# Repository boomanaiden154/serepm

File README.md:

# SeRepM

Like RepRap, but intended to (maybe) actually build itself.

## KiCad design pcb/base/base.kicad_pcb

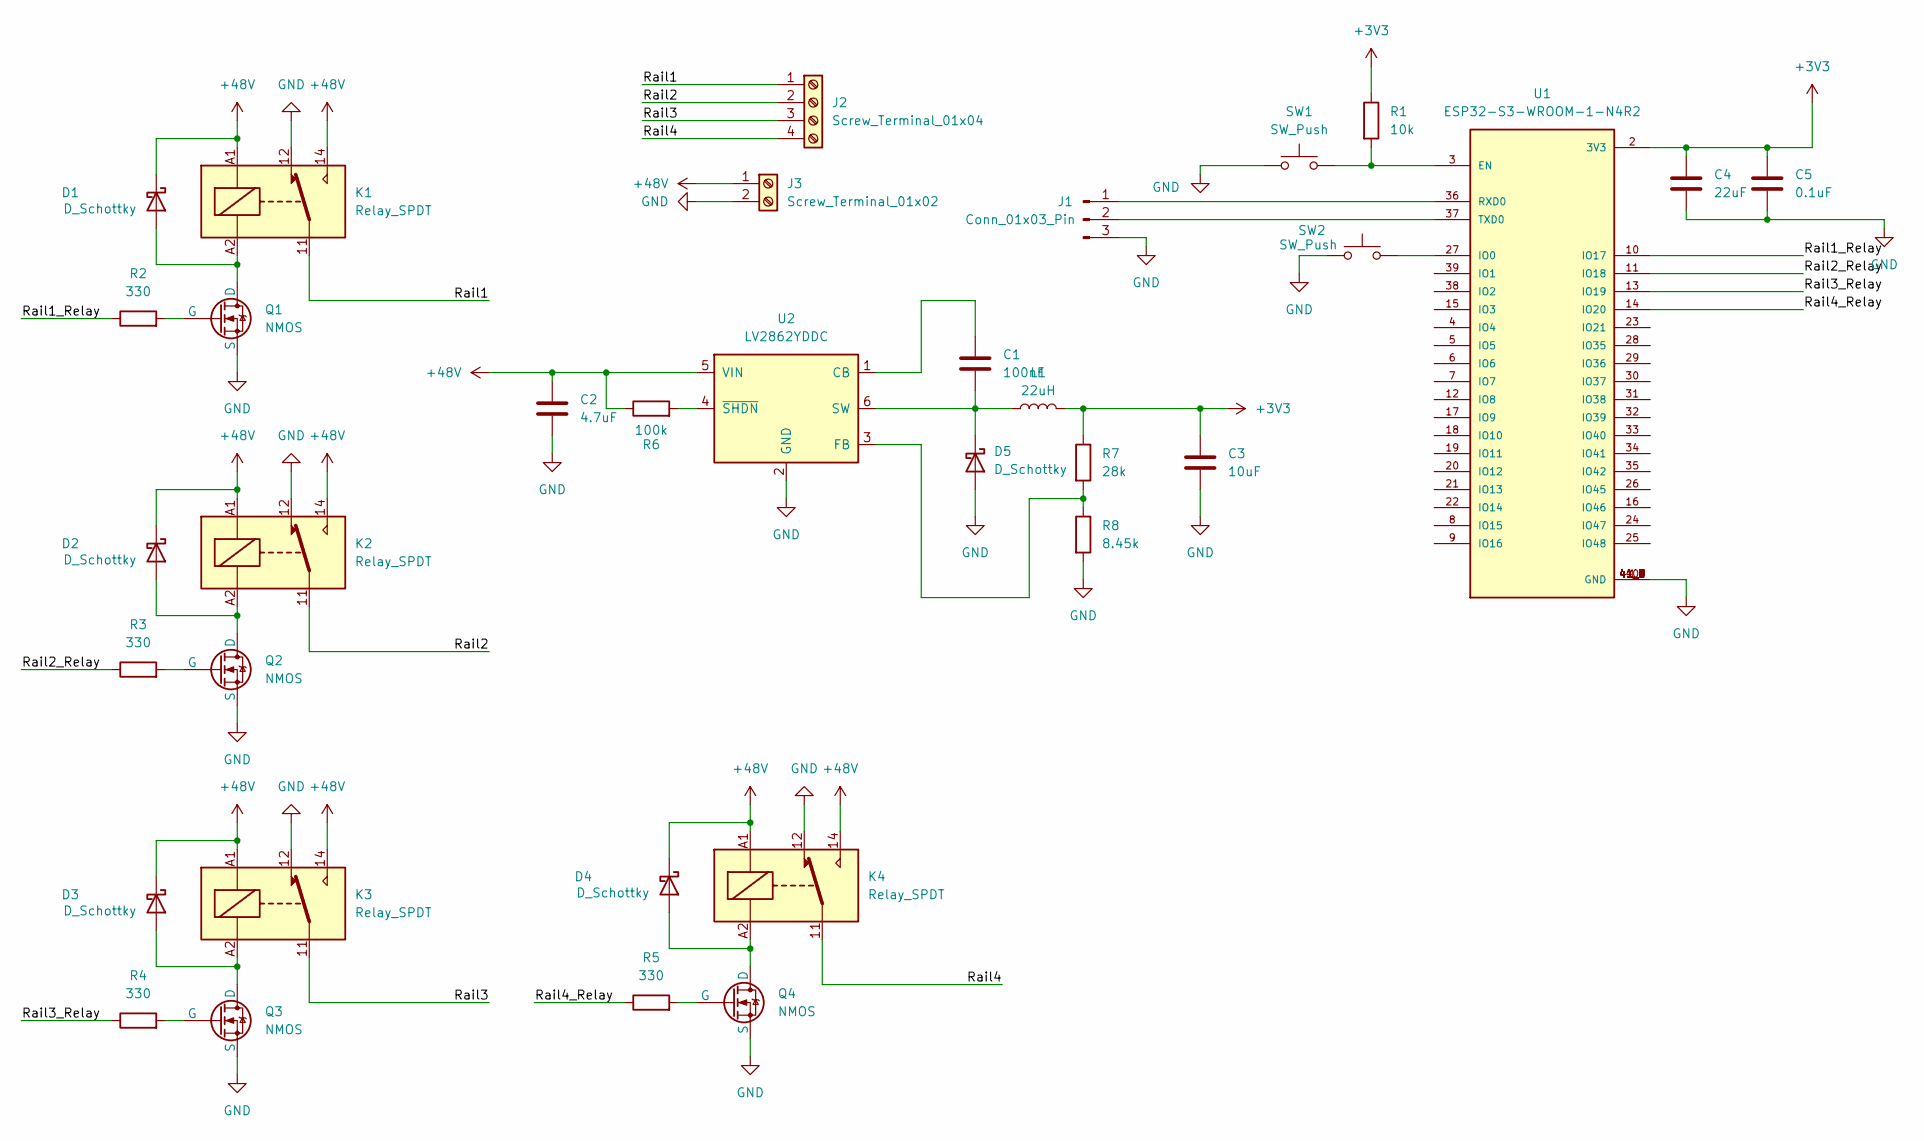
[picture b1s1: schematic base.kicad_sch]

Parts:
C1: 100nF; C_0805_2012Metric_Pad1.18x1.45mm_HandSolder
C2: 4.7uF; C_0805_2012Metric_Pad1.18x1.45mm_HandSolder
C3: 10uF; C_0805_2012Metric_Pad1.18x1.45mm_HandSolder
C4: 22uF; C_0805_2012Metric_Pad1.18x1.45mm_HandSolder
C5: 0.1uF; C_0805_2012Metric_Pad1.18x1.45mm_HandSolder
D1, D2, D3, D4: D_Schottky; SMAFLAT_STPS2170AF_STM
D5: D_Schottky; DIO_DFLS1100-7
J1: Conn_01x03_Pin; PinHeader_1x03_P2.54mm_Vertical
J2: Screw_Terminal_01x04; TE_282836-4
J3: Screw_Terminal_01x02; TE_282836-2
K1, K2, K3, K4: Relay_SPDT; RELAY_PR25-48V-S-360-1C-E
L1: 22uH; IND_TAIYO_NR8040_TAY
Q1, Q2, Q3, Q4: NMOS; SOT-523
R1: 10k; R_0805_2012Metric_Pad1.20x1.40mm_HandSolder
R2, R3, R4, R5: 330; R_0805_2012Metric_Pad1.20x1.40mm_HandSolder
R6: 100k; R_0805_2012Metric_Pad1.20x1.40mm_HandSolder
R7: 28k; R_0805_2012Metric_Pad1.20x1.40mm_HandSolder
R8: 8.45k; R_0805_2012Metric_Pad1.20x1.40mm_HandSolder
SW1, SW2: SW_Push; PTS647SK38SMTR2LFS_CNK
U1: ESP32-S3-WROOM-1-N4R2; XCVR_ESP32-S3-WROOM-1-N4R2; PARTREV v1.0
U2: LV2862YDDC; SOT-23-6

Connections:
+3V3: C3.1, C4.1, C5.1, L1.2, R1.1, R7.1, U1.2 (3V3)
+48V: C2.1, D1.1 (K), D2.1 (K), D3.1 (K), D4.1 (K), J3.1, K1.14, K1.A1, K2.14, K2.A1, K3.14, K3.A1, K4.14, K4.A1, R6.1, U2.5 (VIN)
/Rail1: J2.1, K1.11
/Rail1_Relay: R2.1, U1.10 (IO17)
/Rail2: J2.2, K2.11
/Rail2_Relay: R3.1, U1.11 (IO18)
/Rail3: J2.3, K3.11
/Rail3_Relay: R4.1, U1.13 (IO19)
/Rail4: J2.4, K4.11
/Rail4_Relay: R5.1, U1.14 (IO20)
GND: C2.2, C3.2, C4.2, C5.2, D5.2 (A), J1.3, J3.2, K1.12, K2.12, K3.12, K4.12, Q1.3 (S), Q2.3 (S), Q3.3 (S), Q4.3 (S), R8.2, SW1.1, SW2.1, U1.1 (GND), U1.40 (GND), U1.41_1 (GND), U1.41_2 (GND), U1.41_3 (GND), U1.41_4 (GND), U1.41_5 (GND), U1.41_6 (GND), U1.41_7 (GND), U1.41_8 (GND), U1.41_9 (GND), U2.2 (GND)
unnamed: D1.2 (A), K1.A2, Q1.1 (D)
unnamed: D2.2 (A), K2.A2, Q2.1 (D)
unnamed: D3.2 (A), K3.A2, Q3.1 (D)
unnamed: D4.2 (A), K4.A2, Q4.1 (D)
unnamed: C1.2, D5.1 (K), L1.1, U2.6 (SW)
unnamed: J1.1, U1.36 (RXD0)
unnamed: J1.2, U1.37 (TXD0)
unnamed: Q1.2 (G), R2.2
unnamed: Q2.2 (G), R3.2
unnamed: Q3.2 (G), R4.2
unnamed: Q4.2 (G), R5.2
unnamed: R1.2, SW1.2, U1.3 (EN)
unnamed: SW2.2, U1.27 (IO0)
unnamed: C1.1, U2.1 (CB)
unnamed: R7.2, R8.1, U2.3 (FB)
unnamed: R6.2, U2.4 (~SHDN)

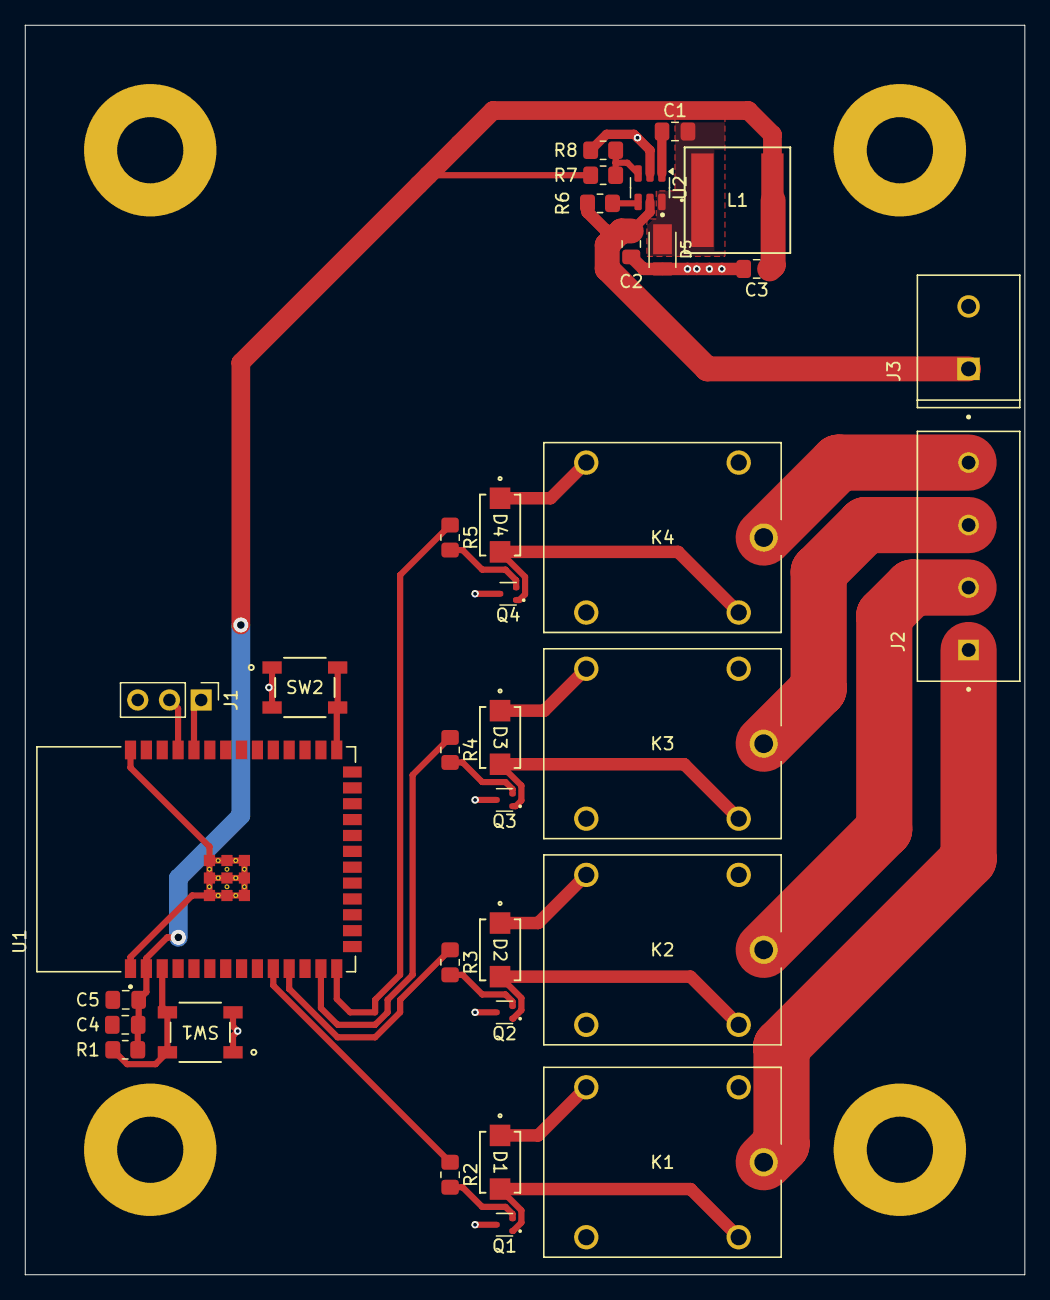
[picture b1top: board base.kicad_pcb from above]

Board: 2 copper layers, 80.0 x 100.0 mm, 34 parts (0 on the bottom side), 27 nets.

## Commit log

2025-06-10 Initial base frame
2025-06-11 Add rail, switch to Assembly4
2025-06-11 Add mounting holes to rails and corners
2025-06-11 Add all rails
2025-06-11 Add small rails on base blocks
2025-06-11 elevate all rails by 5mm
2025-06-11 Add fasteners
2025-06-11 Add rail supports and fasteners
2025-06-11 Model some misc components for the frame
2025-06-16 Misc changes
    Update some main frame components. Also update the README.
2025-06-30 Make SDA match drawings
2025-06-30 Model 4040 Corner
2025-06-30 Add basic frame assembly
2025-06-30 Mount cylinders to frame
2025-06-30 Fix some screw sizing
2025-07-01 Misc Changes
2025-07-01 Add Basic Solenoid Model
2025-07-01 Add bottom corner solenoids
2025-07-01 Add top corners
2025-07-01 Fix incorrect screw size
2025-07-01 Add main top rails
2025-07-01 Add Rail Ends
2025-07-05 Roughly Model Viair 65C
    This patch roughly models the Viair 65C. The model doesn't need to be
    super accurate and cannot be given the provided dimensional drawing
    shows basically nothing (although this model is accurate to that).
2025-07-05 Model 4V220 Solenoid
2025-07-06 Model 2V025 Solenoid
2025-07-06 Fix some holes in 2V025
2025-07-06 Mount compressor to frame
2025-07-06 Mount 4V220s to frame
2025-07-06 Mount 2V025 Solenoid
2025-07-06 Start designing base PCB
2025-07-12 Finish most of the PCB design
2025-07-27 Some PCB changes
2025-07-27 Finish schematic, add footprints
2025-07-27 Finish PCB design
2025-07-27 Repour some zones
2025-07-27 Update some trace widths
2026-03-30 Change Rail Screws to M2
    This allows the use of heat set inserts on all the connections.
2026-03-30 Finish M2 Adjustment in FrameAssembly
2026-03-30 misc
2026-03-30 Add solenoid cutout
2026-03-30 Some initial work on the carriage
2026-04-04 Add RailEnd fixture
2026-04-05 Add square base fixture
    So that I can play with the square tube steel that I have before I
    acquire angle steel.
2026-04-05 Mostly finish carriage design
    Mostly finished. Probably a couple minor issues to figure out, and a
    wheel drive mechanism still needs implementation.
2026-04-05 Add W625ZZ drive center
    Allows for the W625ZZ wheels to be driven using a d shaft.
    Works reasonably well when printed on a raft on my printer. Needs a raft
    because of first layer overextrusion problems.
2026-04-05 Add 2020 extrusion mount to carriage
    This will allow for a stepper motor to be mounted in between two
    carriages, transferring power to both of them.
    This will require additonal tensioning equipment, but I could not come
    up with a much easier way to do this.
2026-04-05 Misc fixes for carriage assembly
    insert sizing
    extra object in assembly
2026-04-05 Model 2020 extrusion for carraige connection.
    Four holes to connector to the carriage assembly, 200mm long to make the
    combined assembly ~420mm long, which should take up most of the side
    length.
2026-04-05 Update Carriage Assembly
    Add extrusion, mount with screws.
    Change the attachment for one wheel to use bearings which will allow
    switching the axle for a d-shaft which will allow power transmission.
2026-04-06 Model 2GT Pulleys
    These are needed for driving the carriage wheels.
2026-04-06 Model D Shaft for carriage
2026-04-06 Model NEMA17 Stepper Motor
2026-05-31 Minor rail modifications
    Add holes to mount SC1.5-4 nose terminals.
    Also add a technical drawing that I can reference when cutting steel.
2026-06-01 Initial Carriage Idler holder design
2026-06-01 Fix dimensions of side base piece
    The holes were too small (0.1mm on the radius) which made the heat set
    inserts not fit well.
    One of the holes was also not constrained correctly, so was misaligned.
    The holes were also all only 2mm deep instead of 3mm deep.
    Would have been nice to figure this out before doing a 9 hour print...
2026-06-01 Fix center dimensions
    Same issues as with the side. Non-constrained holes, and the hole
    dimensions were not correct. Fix it now while I remember.
2026-06-07 Fix rail fixture dimensions
    The hole size was off because I was making incorrect assumptions about
    the location of the hole relative to the bottom corners. This patch
    changes the dimensions to work and also adds an assembly which makes it
    easy to verify that the holes do indeed line up.
2026-06-07 Add wire mount to other side of rail
    To ensure that there is always a hole on the inside of the frame.
